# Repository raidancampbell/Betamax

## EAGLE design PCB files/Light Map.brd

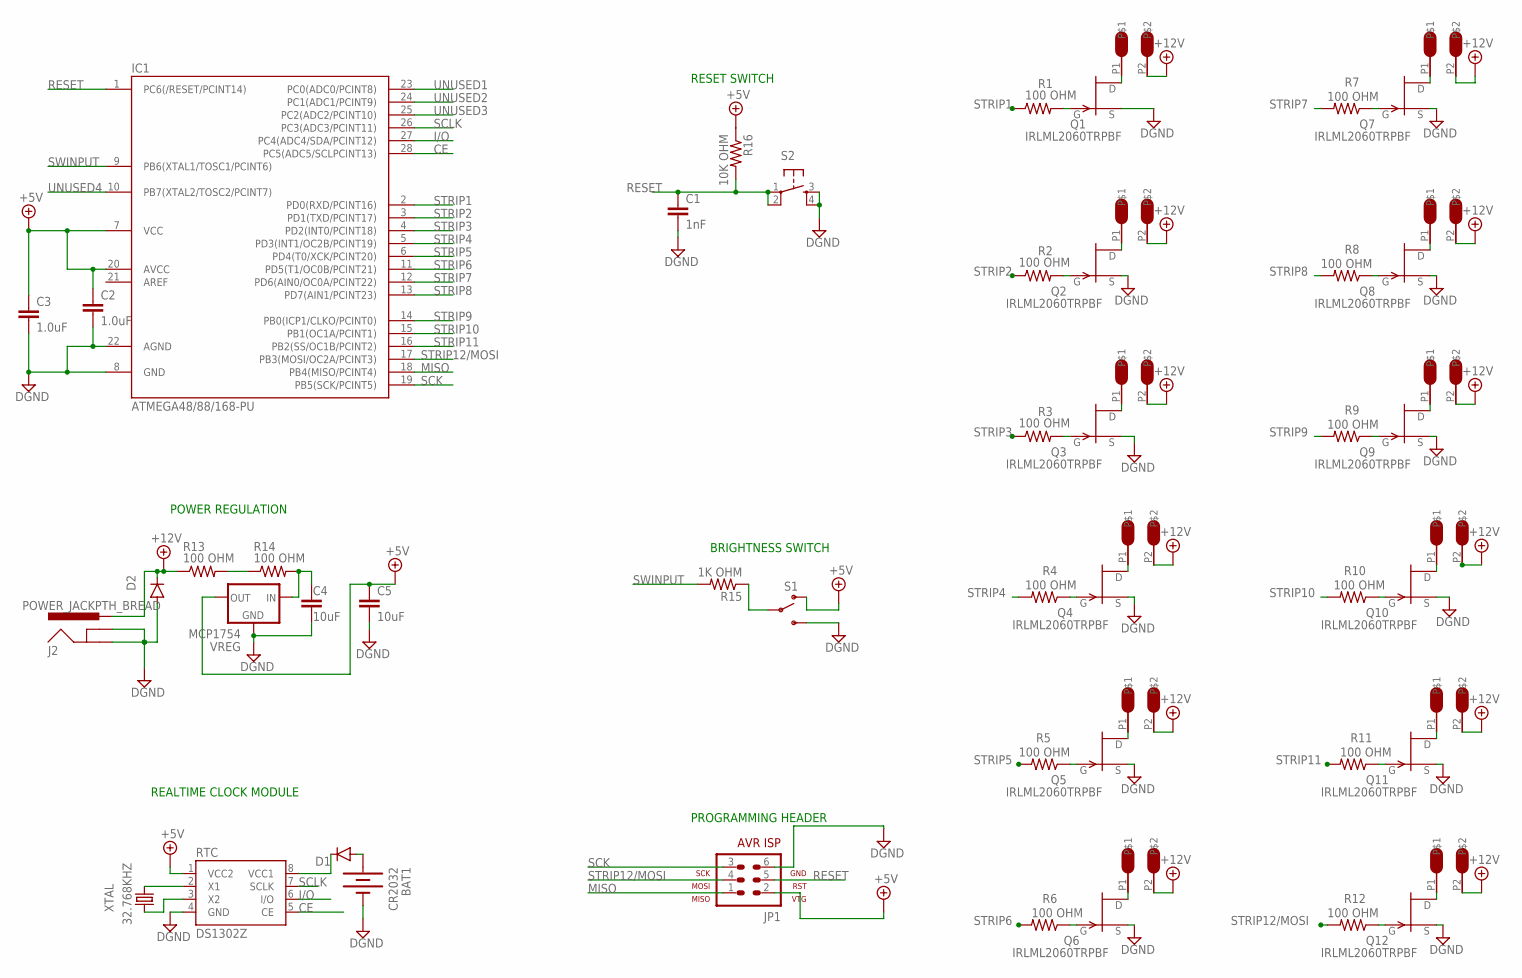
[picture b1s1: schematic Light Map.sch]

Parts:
BAT1: CR2032; BATTCOM_20MM_PTH
C1: 1nF; 1206
C2, C3: 1.0uF; 1206
C4, C5: 10uF; 1206
D1: DIODE; DIODE-1N4001-KIT
D2: DIODESMA; SMA-DIODE
IC1: ATMEGA48/88/168-PU; DIL28-3
J2: POWER_JACKPTH_BREAD; POWER_JACK_PTH_BREAD
JP1: AVR-ISP-6
Q1, Q2, Q3, Q4, Q5, Q6, Q7, Q8, Q9, Q10, Q11, Q12: IRLML2060TRPBF; SOT23
R1, R2, R3, R4, R5, R6, R7, R8, R9, R10, R11, R12, R13, R14: 100 OHM; 1206
R15: 1K OHM; 1206
R16: 10K OHM; 1206
RTC: DS1302Z; SO08
S1: SWITCH-SPDTPTH_LOCK; SWITCH-SPDT_LOCK.007S
S2: TAC_SWITCHPTH; TACTILE-PTH
U$1, U$2, U$3, U$4, U$5, U$6, U$7, U$8, U$9, U$10, U$11, U$12: OSTTE020104
VREG: MCP1754; SOT23
XTAL: 32.768KHZ; TC26H

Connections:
+5V: C2.1, C3.1, C5.1, IC1.7 (VCC), IC1.20 (AVCC), JP1.2, R16.1, RTC.1 (VCC2), S1.1 (O), VREG.2 (OUT)
+12V: D2.C, J2.PWR, R13.1, U$1.P2, U$2.P2, U$3.P2, U$4.P2, U$5.P2, U$6.P2, U$7.P2, U$8.P2, U$9.P2, U$10.P2, U$11.P2, U$12.P2
CE: IC1.28 (PC5(ADC5/SCLPCINT13)), RTC.5 (CE)
DGND: BAT1.2 (-), C1.2, C2.2, C3.2, C4.2, C5.2, D2.A, IC1.8 (GND), IC1.22 (AGND), J2.GND, J2.GNDBREAK, JP1.6, Q1.2 (S), Q2.2 (S), Q3.2 (S), Q4.2 (S), Q5.2 (S), Q6.2 (S), Q7.2 (S), Q8.2 (S), Q9.2 (S), Q10.2 (S), Q11.2 (S), Q12.2 (S), RTC.4 (GND), S1.3 (S), S2.3, S2.4, VREG.1 (GND)
I/O: IC1.27 (PC4(ADC4/SDA/PCINT12)), RTC.6 (I/O)
MISO: IC1.18 (PB4(MISO/PCINT4)), JP1.1
unnamed: D1.C, RTC.8 (VCC1)
unnamed: BAT1.1 (+), D1.A
unnamed: C4.1, R14.2, VREG.3 (IN)
unnamed: Q1.1 (G), R1.2
unnamed: Q2.1 (G), R2.2
unnamed: Q3.1 (G), R3.2
unnamed: Q4.1 (G), R4.1
unnamed: Q5.1 (G), R5.1
unnamed: Q10.1 (G), R10.1
unnamed: Q6.1 (G), R6.1
unnamed: Q7.1 (G), R7.1
unnamed: Q8.1 (G), R8.1
unnamed: Q9.1 (G), R9.1
unnamed: Q11.1 (G), R11.1
unnamed: Q1.3 (D), U$1.P1
unnamed: Q2.3 (D), U$5.P1
unnamed: Q3.3 (D), U$4.P1
unnamed: Q4.3 (D), U$3.P1
unnamed: Q5.3 (D), U$2.P1
unnamed: Q6.3 (D), U$6.P1
unnamed: Q7.3 (D), U$7.P1
unnamed: Q8.3 (D), U$8.P1
unnamed: Q9.3 (D), U$9.P1
unnamed: Q10.3 (D), U$10.P1
unnamed: Q11.3 (D), U$11.P1
unnamed: Q12.3 (D), U$12.P1
unnamed: Q12.1 (G), R12.1
unnamed: R13.2, R14.1
unnamed: R15.1, S1.2
RESET: C1.1, IC1.1 (PC6(/RESET/PCINT14)), JP1.5, R16.2, S2.1, S2.2
SCK: IC1.19 (PB5(SCK/PCINT5)), JP1.3
SCLK: IC1.26 (PC3(ADC3/PCINT11)), RTC.7 (SCLK)
STRIP1: IC1.2 (PD0(RXD/PCINT16)), R1.1
STRIP2: IC1.3 (PD1(TXD/PCINT17)), R2.1
STRIP3: IC1.4 (PD2(INT0/PCINT18)), R3.1
STRIP4: IC1.5 (PD3(INT1/OC2B/PCINT19)), R4.2
STRIP5: IC1.6 (PD4(T0/XCK/PCINT20)), R5.2
STRIP6: IC1.11 (PD5(T1/OC0B/PCINT21)), R6.2
STRIP7: IC1.12 (PD6(AIN0/OC0A/PCINT22)), R7.2
STRIP8: IC1.13 (PD7(AIN1/PCINT23)), R8.2
STRIP9: IC1.14 (PB0(ICP1/CLKO/PCINT0)), R9.2
STRIP10: IC1.15 (PB1(OC1A/PCINT1)), R10.2
STRIP11: IC1.16 (PB2(SS/OC1B/PCINT2)), R11.2
STRIP12/MOSI: IC1.17 (PB3(MOSI/OC2A/PCINT3)), JP1.4, R12.2
SWINPUT: IC1.9 (PB6(XTAL1/TOSC1/PCINT6)), R15.2
UNUSED1: IC1.23 (PC0(ADC0/PCINT8))
UNUSED2: IC1.24 (PC1(ADC1/PCINT9))
UNUSED3: IC1.25 (PC2(ADC2/PCINT10))
UNUSED4: IC1.10 (PB7(XTAL2/TOSC2/PCINT7))
XTAL1: RTC.3 (X2), XTAL.1
XTAL2: RTC.2 (X1), XTAL.2

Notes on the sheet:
BRIGHTNESS SWITCH
RESET SWITCH
PROGRAMMING HEADER
POWER REGULATION
REALTIME CLOCK MODULE

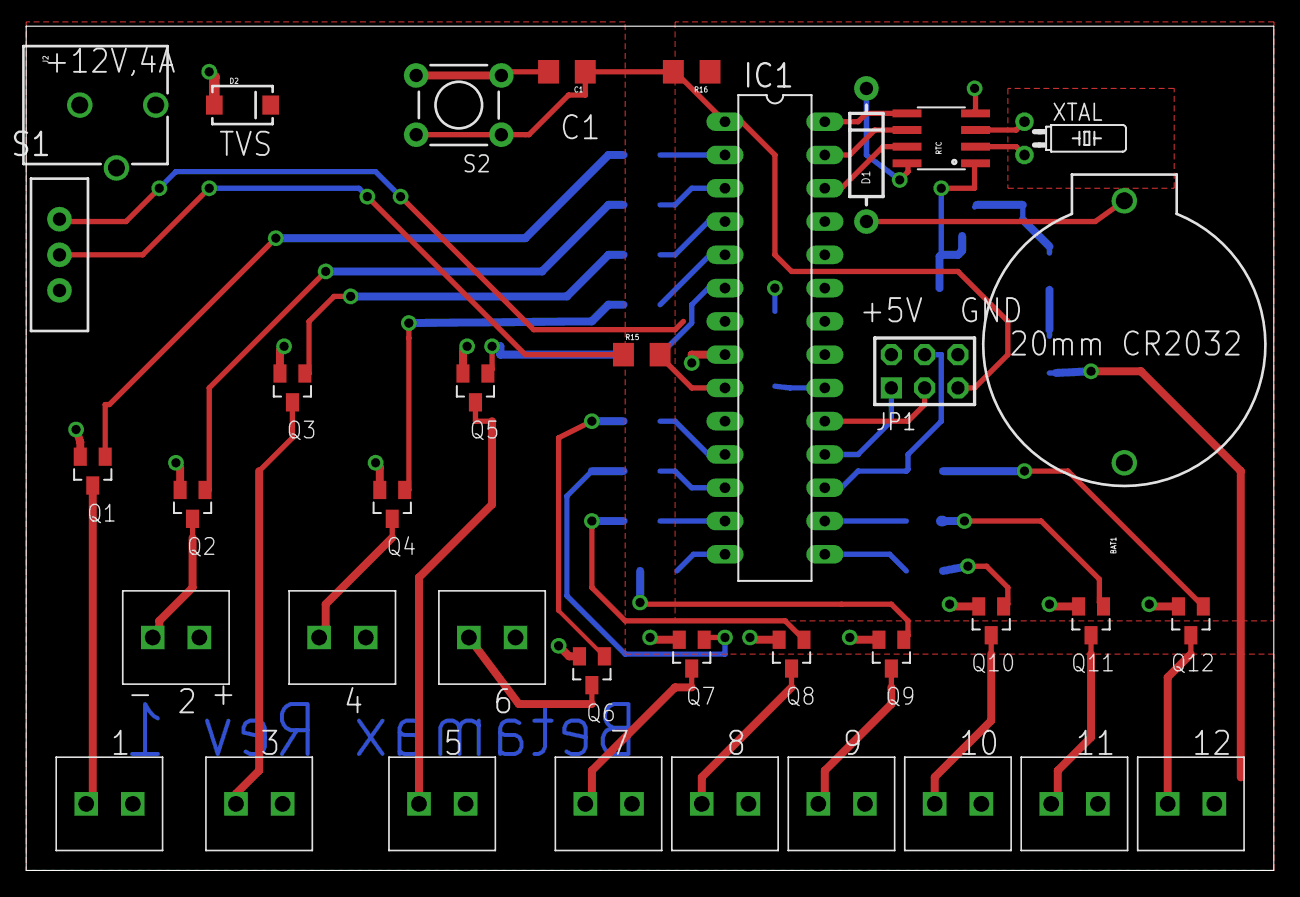
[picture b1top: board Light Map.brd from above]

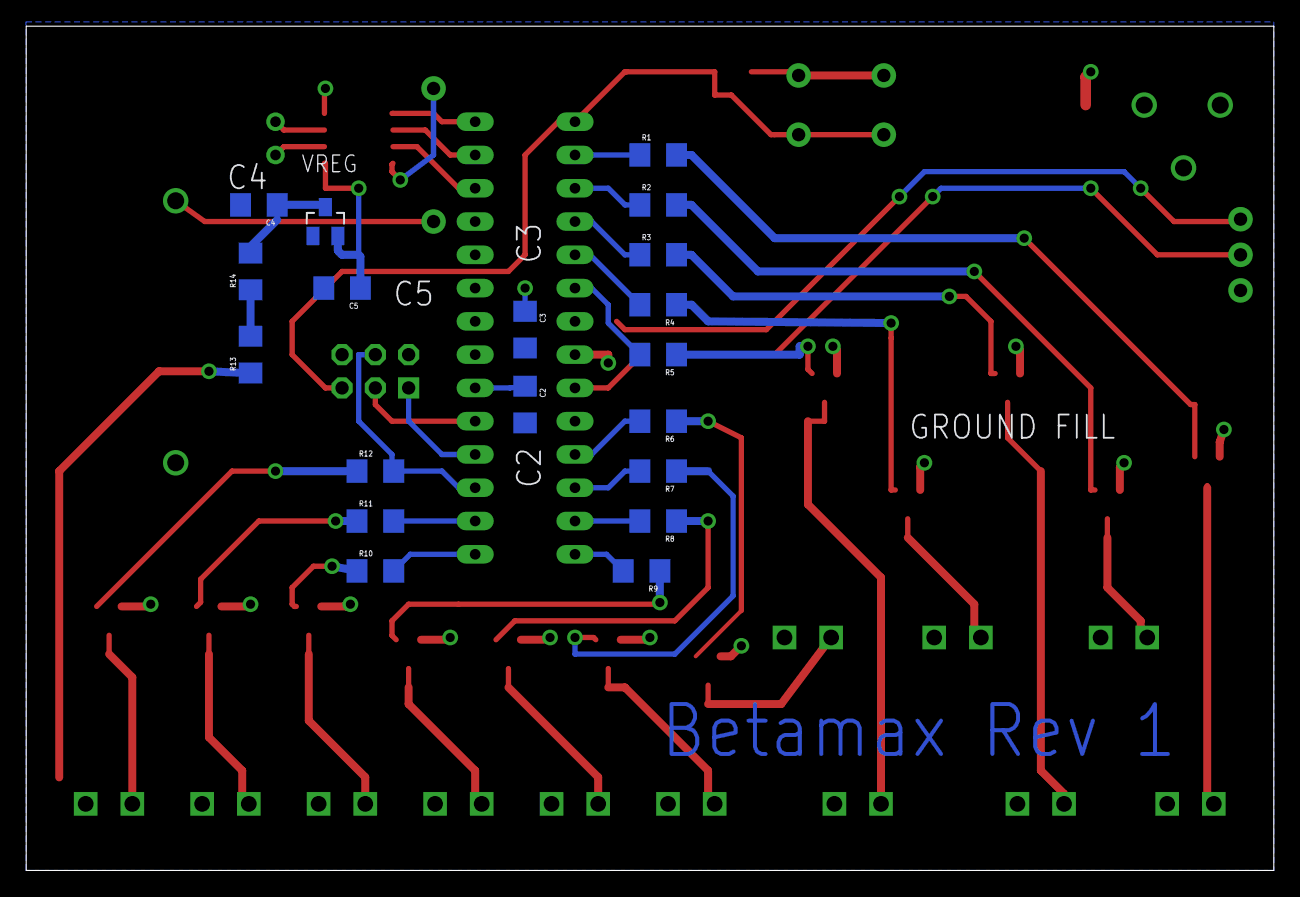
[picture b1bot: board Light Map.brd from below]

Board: 2 copper layers, 95.2 x 64.4 mm, 56 parts (19 on the bottom side), 53 nets.

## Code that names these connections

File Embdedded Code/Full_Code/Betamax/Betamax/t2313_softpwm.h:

// This file has been prepared for Doxygen automatic documentation generation.
/*! \file ********************************************************************
*
* Atmel Corporation
*
* - File              : t2313_softpwm.h
* - Compiler          : IAR EWAAVR 4.11A or GCC 3.4.3
*
* - Support mail      : avr@atmel.com
*
* - Supported devices : ATtiny2313.
*
* - AppNote           : AVR136 - Low-Jitter Multi-Channel Software PWM
*
* - Description       : Header file for t2313_softpwm.c
*
* $Revision: 1.2 $
* $Date: Tuesday, December 20, 2005 14:11:04 UTC $
*****************************************************************************/

/*! \brief  Select or deselect ISR Timing Debugging, 0 = disabled, 1 = enabled
 */
#define DEBUG 0

//! Compiler specific defines
#if defined(__ICCAVR__)
  // correct an IAR definition for Watchdog Timer Control Register,
  // may not be needed in later versions of IAR or for other AVR devices.
  #define WDTCSR  WDTCR
#elif __GNUC__ > 0
  // redefine some macros
  #define __C_task int
  #define __enable_interrupt()  sei()
  #define __watchdog_reset()    wdt_reset()
#endif

//! Pin mappings
#define CHMAX       12    // maximum number of PWM channels
#define PWMDEFAULT  0x80  // default PWM value at start up for all channels

#define CH0_CLEAR (pinlevelD &= ~(1 << PD0)) // map CH0 to PD0
#define CH1_CLEAR (pinlevelD &= ~(1 << PD1)) // map CH1 to PD1
#define CH2_CLEAR (pinlevelD &= ~(1 << PD2)) // map CH2 to PD2
#define CH3_CLEAR (pinlevelD &= ~(1 << PD3)) // map CH3 to PD3
#define CH4_CLEAR (pinlevelD &= ~(1 << PD4)) // map CH4 to PD4
#define CH5_CLEAR (pinlevelD &= ~(1 << PD5)) // map CH5 to PD5
#define CH6_CLEAR (pinlevelD &= ~(1 << PD6)) // map CH6 to PD6
#define CH7_CLEAR (pinlevelD &= ~(1 << PD7)) // map CH7 to PD7

#define CH8_CLEAR (pinlevelB &= ~(1 << PB0)) // map CH8 to PB0
#define CH9_CLEAR (pinlevelB &= ~(1 << PB1)) // map CH9 to PB1
#define CH10_CLEAR (pinlevelB &= ~(1 << PB2)) // map CH10 to PB2
#define CH11_CLEAR (pinlevelB &= ~(1 << PB3)) // map CH11 to PB3

//! Set bits corresponding to pin usage above
#define PORTB_MASK  (1 << PB0)|(1 << PB1)|(1 << PB2)|(1 << PB3)
#define PORTD_MASK  (1 << PD0)|(1 << PD1)|(1 << PD2)|(1 << PD3)|(1 << PD4)|(1 << PD5)|(1 << PD6)|(1 << PD7)

#define DEBUGPIN_ON   PORTB |= (1 << PB7)
#define DEBUGPIN_OFF  PORTB &= ~(1 << PB7)
#define DEBUGSET      DDRB |= (1 << DDB7)

//! prototypes
void Init(void);
unsigned char HexToASCII (unsigned char ch);
unsigned char GetNextChar(void);
void ManualControl(void);
void DebugMonitor(void);
void USART0_Transmit( unsigned char data );
unsigned char USART0_Receive( void );

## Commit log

2015-07-13 initial commit - light algorithm working as per http://users.electromagnetic.net/bu/astro/iyf-calc.php?lat=41.48&long=81.68
2015-07-13 cleaning - code de-linted
2015-07-13 folder restructuring
2015-07-13 added PCB files and some base code
2015-07-13 repo cleaning
2018-10-16 remove IDE files

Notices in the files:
parts and their libraries:
SparkFun-Passives: Licensing: Creative Commons ShareAlike 4.0 International - https://creativecommons.org/licenses/by-sa/4.0
SparkFun: Licensing: CC v3.0 Share-Alike You are welcome to use this library for commercial purposes.
